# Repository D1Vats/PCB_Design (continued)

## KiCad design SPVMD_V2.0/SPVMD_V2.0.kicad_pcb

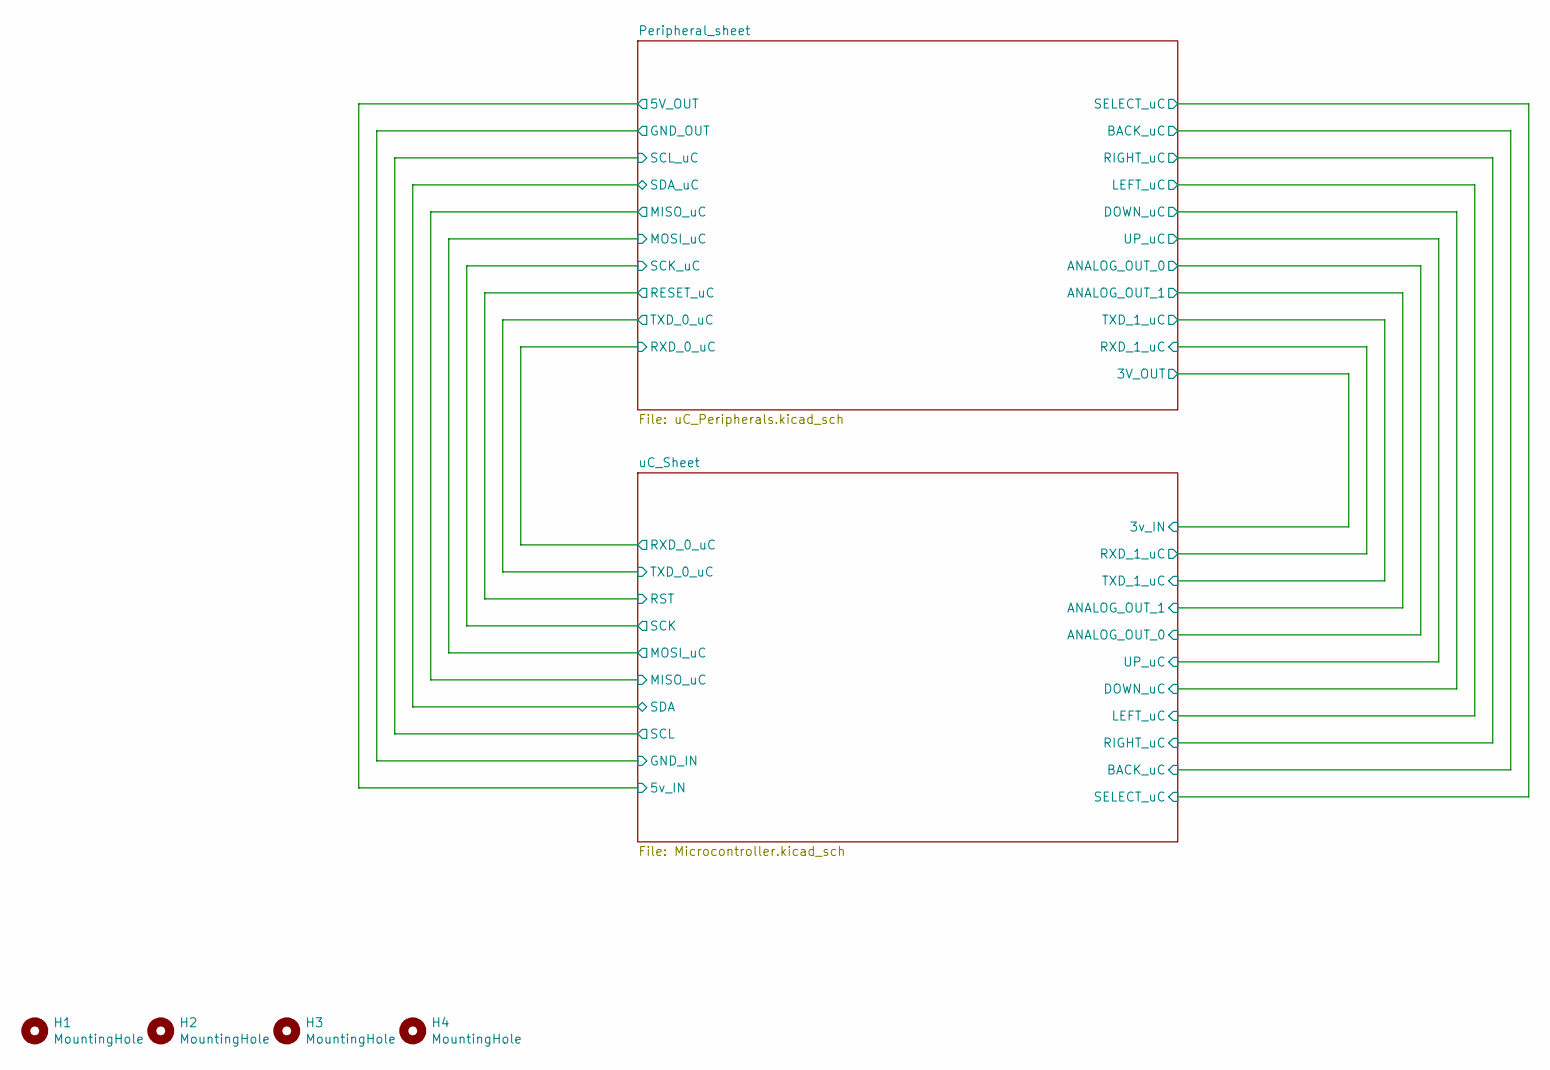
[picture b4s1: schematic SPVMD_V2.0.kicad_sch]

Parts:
H1, H2, H3, H4: MountingHole; MountingHole_3.2mm_M3

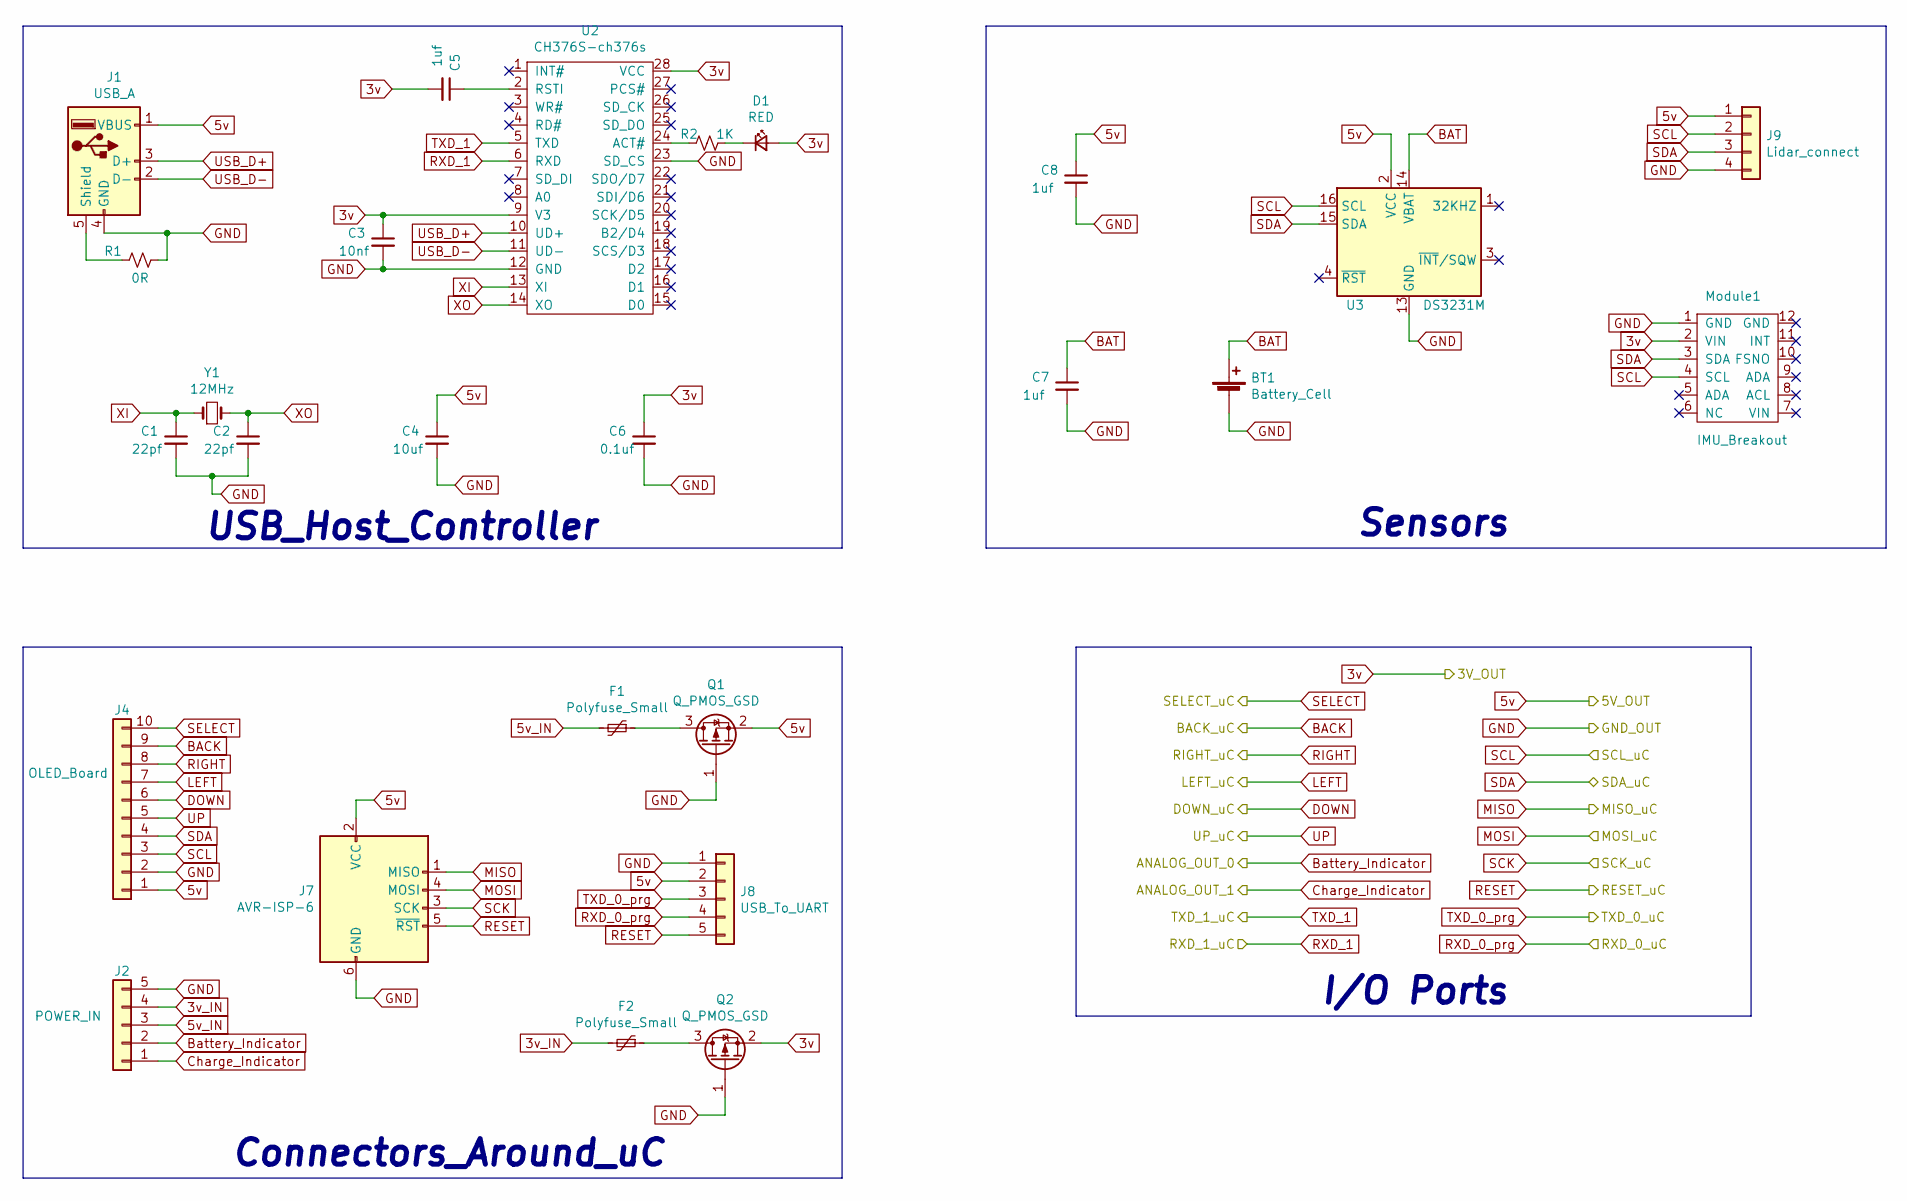
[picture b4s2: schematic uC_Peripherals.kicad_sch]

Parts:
BT1: Battery_Cell; BatteryHolder_Keystone_104_1x23mm
C1, C2: 22pf; C_0805_2012Metric
C3: 10nf; C_0805_2012Metric
C4: 10uf; C_0805_2012Metric
C5, C7, C8: 1uf; C_0805_2012Metric
C6: 0.1uf; C_0805_2012Metric
D1: RED; LED_0805_2012Metric
F1, F2: Polyfuse_Small; Fuse_0805_2012Metric_Pad1.15x1.40mm_HandSolder
J1: USB_A; USB_A_Molex_67643_Horizontal
J2: POWER_IN; SolderWire-0.1sqmm_1x05_P3.6mm_D0.4mm_OD1mm_Relief
J4: OLED_Board; Hirose_FH12-10S-0.5SH_1x10-1MP_P0.50mm_Horizontal
J7: AVR-ISP-6; PinHeader_2x03_P2.54mm_Vertical
J8: USB_To_UART; PinSocket_1x05_P2.54mm_Vertical
J9: Lidar_connect; SolderWire-0.1sqmm_1x04_P3.6mm_D0.4mm_OD1mm_Relief
Module1: IMU_Breakout; DIP-12_925_ELL
Q1, Q2: Q_PMOS_GSD; SOT-23W_Handsoldering
R1: 0R; R_0805_2012Metric
R2: 1K; R_0805_2012Metric
U2: CH376S-ch376s; SOIC-28W_7.5x17.9mm_P1.27mm
U3: DS3231M; SOIC-16W_7.5x10.3mm_P1.27mm
Y1: 12MHz; Crystal_HC49-4H_Vertical

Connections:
3V_IN: C3.1, C5.2, C6.1, D1.2 (A), Module1.2 (VIN), Q2.2 (S), U2.9 (V3), U2.28 (VCC); also elsewhere on the board
3v_IN: F2.2, J2.4
5v: C4.1, C8.1, J1.1 (VBUS), J4.1, J7.2 (VCC), J8.2, J9.1, Q1.2 (S), U3.2 (VCC); also elsewhere on the board
5v_IN: F1.2, J2.3
BACK: J4.9; also elsewhere on the board
BAT: BT1.1 (+), C7.1, U3.14 (VBAT)
Battery_Indicator: J2.2; also elsewhere on the board
Charge_Indicator: J2.1; also elsewhere on the board
DOWN: J4.6; also elsewhere on the board
GND: BT1.2 (-), C1.2, C2.2, C3.2, C4.2, C6.2, C7.2, C8.2, J1.4 (GND), J2.5, J4.2, J7.6 (GND), J8.1, J9.4, Module1.1 (GND), Q1.1 (G), Q2.1 (G), R1.1, U2.12 (GND), U2.23 (SD_CS), U3.5 (GND), U3.6 (GND), U3.7 (GND), U3.8 (GND), U3.9 (GND), U3.10 (GND), U3.11 (GND), U3.12 (GND), U3.13 (GND); also elsewhere on the board
LEFT: J4.7; also elsewhere on the board
LV_RXD_1: U2.5 (TXD); also elsewhere on the board
LV_TXD_1: U2.6 (RXD); also elsewhere on the board
MISO: J7.1 (MISO); also elsewhere on the board
MOSI: J7.4 (MOSI); also elsewhere on the board
unnamed: C5.1, U2.2 (RSTI)
unnamed: D1.1 (K), R2.1
unnamed: F1.1, Q1.3 (D)
unnamed: F2.1, Q2.3 (D)
unnamed: J1.5 (Shield), R1.2
unnamed: R2.2, U2.24 (ACT#)
RESET: J7.5 (~RST), J8.5; also elsewhere on the board
RIGHT: J4.8; also elsewhere on the board
RXD_0: J8.3; also elsewhere on the board
RXD_0_prg: J8.4; also elsewhere on the board
SCK: J7.3 (SCK); also elsewhere on the board
SCL: J4.3, J9.2, Module1.4 (SCL), U3.16 (SCL); also elsewhere on the board
SDA: J4.4, J9.3, Module1.3 (SDA), U3.15 (SDA); also elsewhere on the board
SELECT: J4.10; also elsewhere on the board
UP: J4.5; also elsewhere on the board
USB_D+: J1.3 (D+), U2.10 (UD+)
USB_D-: J1.2 (D-), U2.11 (UD-)
XI: C1.1, U2.13 (XI), Y1.1
XO: C2.1, U2.14 (XO), Y1.2

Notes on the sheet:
Connectors_Around_uC
USB_Host_Controller
I/O Ports
Sensors

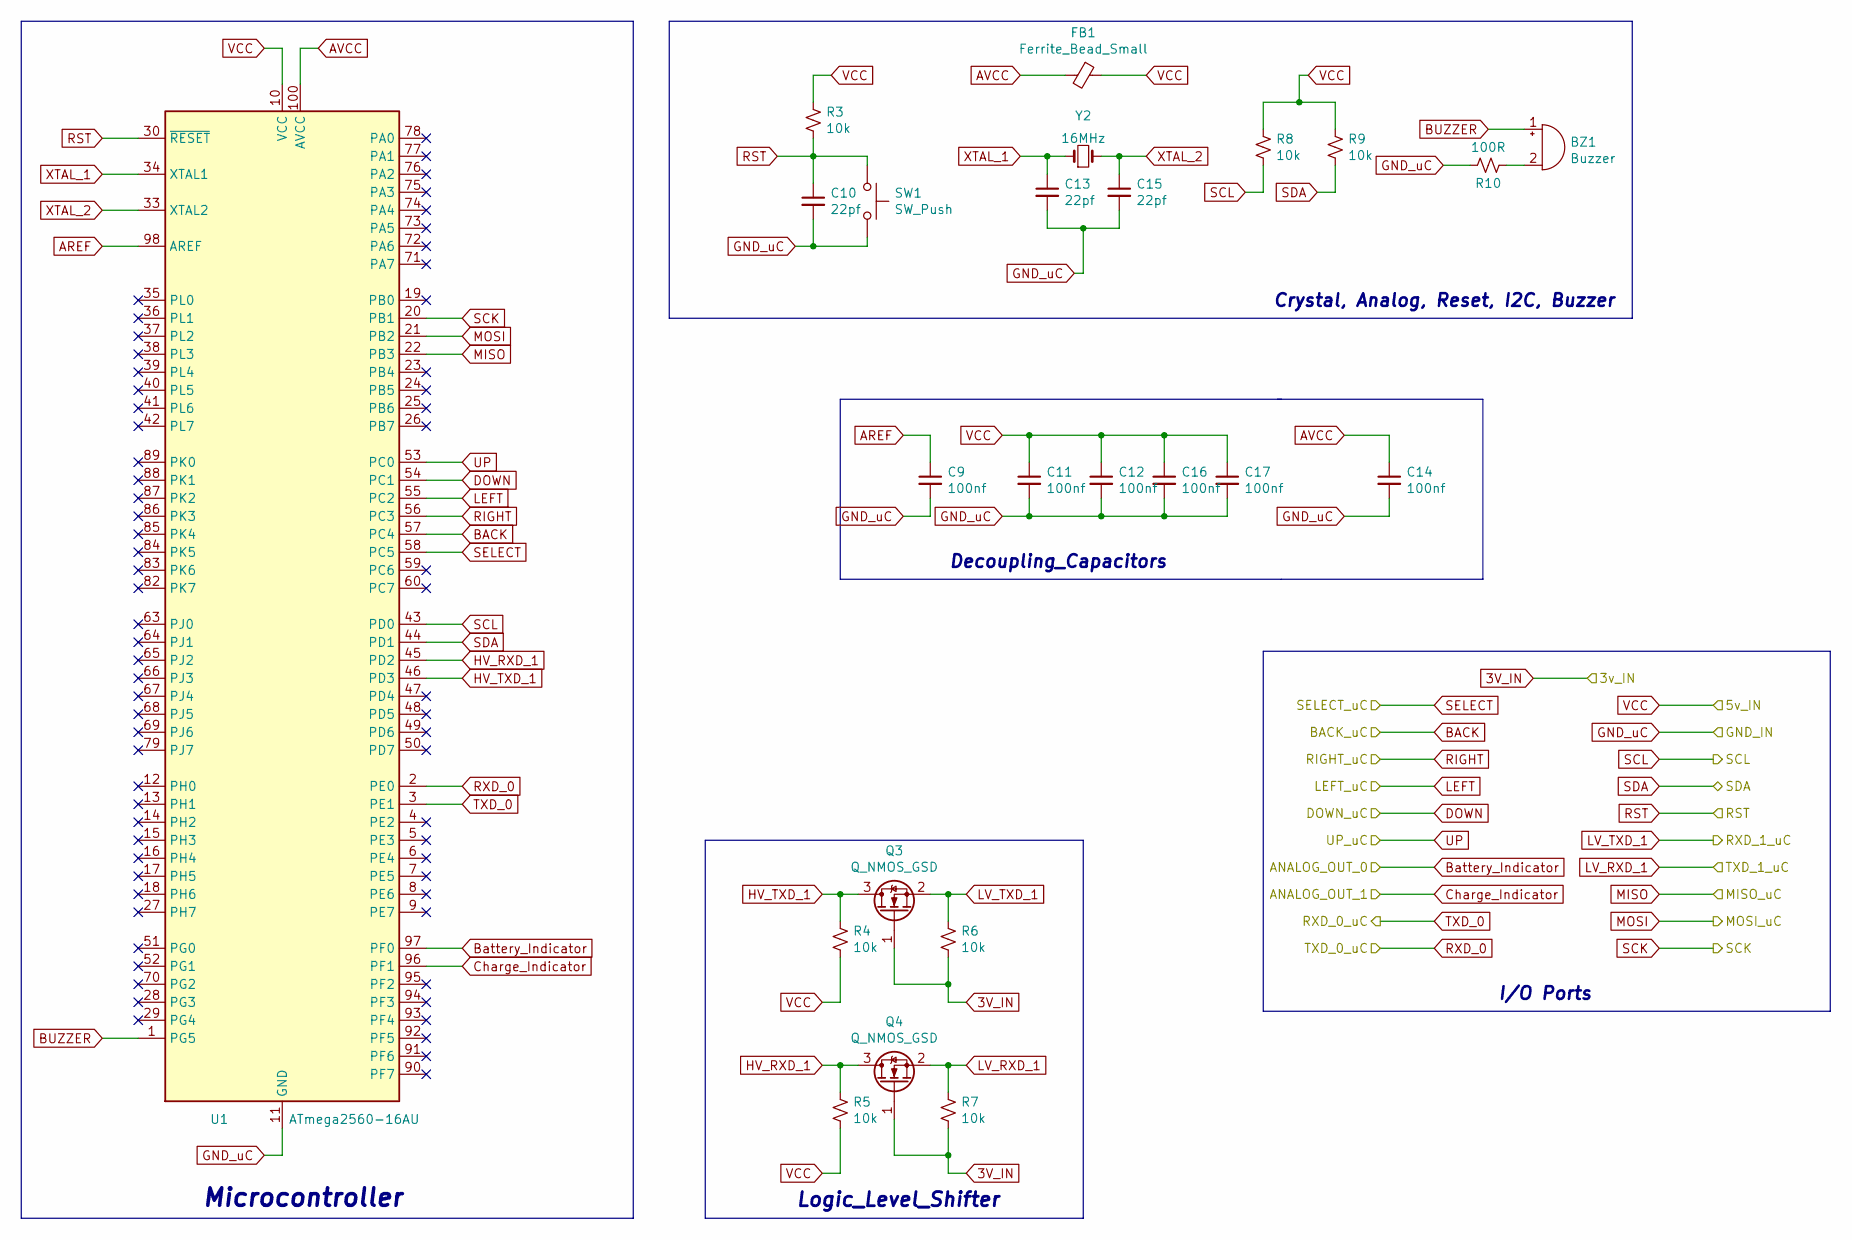
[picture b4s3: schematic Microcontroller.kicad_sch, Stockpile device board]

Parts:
BZ1: Buzzer; Buzzer_12x9.5RM7.6
C9, C11, C12, C14, C16, C17: 100nf; C_0805_2012Metric
C10, C13, C15: 22pf; C_0805_2012Metric
FB1: Ferrite_Bead_Small; R_0805_2012Metric
Q3, Q4: Q_NMOS_GSD; SOT-23W_Handsoldering
R3, R4, R5, R6, R7, R8, R9: 10k; R_0805_2012Metric
R10: 100R; R_0805_2012Metric
SW1: SW_Push; SW_PUSH_6mm
U1: ATmega2560-16AU; TQFP-100_14x14mm_P0.5mm
Y2: 16MHz; Crystal_HC49-4H_Vertical

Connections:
3V_IN: Q3.1 (G), Q4.1 (G), R6.2, R7.2; also elsewhere on the board
5v: C11.1, C12.1, C16.1, C17.1, FB1.1, R3.1, R4.2, R5.2, R8.1, R9.1, U1.10 (VCC), U1.31 (VCC), U1.61 (VCC), U1.80 (VCC); also elsewhere on the board
AREF: C9.1, U1.98 (AREF)
AVCC: C14.1, FB1.2, U1.100 (AVCC)
BACK: U1.57 (PC4); also elsewhere on the board
BUZZER: BZ1.1 (-), U1.1 (PG5)
Battery_Indicator: U1.97 (PF0); also elsewhere on the board
Charge_Indicator: U1.96 (PF1); also elsewhere on the board
DOWN: U1.54 (PC1); also elsewhere on the board
GND: C9.2, C10.2, C11.2, C12.2, C13.2, C14.2, C15.2, C16.2, C17.2, R10.2, SW1.2, U1.11 (GND), U1.32 (GND), U1.62 (GND), U1.81 (GND), U1.99 (GND); also elsewhere on the board
HV_RXD_1: Q4.3 (D), R5.1, U1.45 (PD2)
HV_TXD_1: Q3.3 (D), R4.1, U1.46 (PD3)
LEFT: U1.55 (PC2); also elsewhere on the board
LV_RXD_1: Q4.2 (S), R7.1; also elsewhere on the board
LV_TXD_1: Q3.2 (S), R6.1; also elsewhere on the board
MISO: U1.22 (PB3); also elsewhere on the board
MOSI: U1.21 (PB2); also elsewhere on the board
unnamed: BZ1.2 (+), R10.1
RESET: C10.1, R3.2, SW1.1, U1.30 (~RESET); also elsewhere on the board
RIGHT: U1.56 (PC3); also elsewhere on the board
RXD_0: U1.2 (PE0); also elsewhere on the board
RXD_0_prg: U1.3 (PE1); also elsewhere on the board
SCK: U1.20 (PB1); also elsewhere on the board
SCL: R8.2, U1.43 (PD0); also elsewhere on the board
SDA: R9.2, U1.44 (PD1); also elsewhere on the board
SELECT: U1.58 (PC5); also elsewhere on the board
UP: U1.53 (PC0); also elsewhere on the board
XTAL_1: C13.1, U1.34 (XTAL1), Y2.1
XTAL_2: C15.1, U1.33 (XTAL2), Y2.2

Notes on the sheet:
Decoupling_Capacitors
Microcontroller
Logic_Level_Shifter
I/O Ports
Crystal, Analog, Reset, I2C, Buzzer

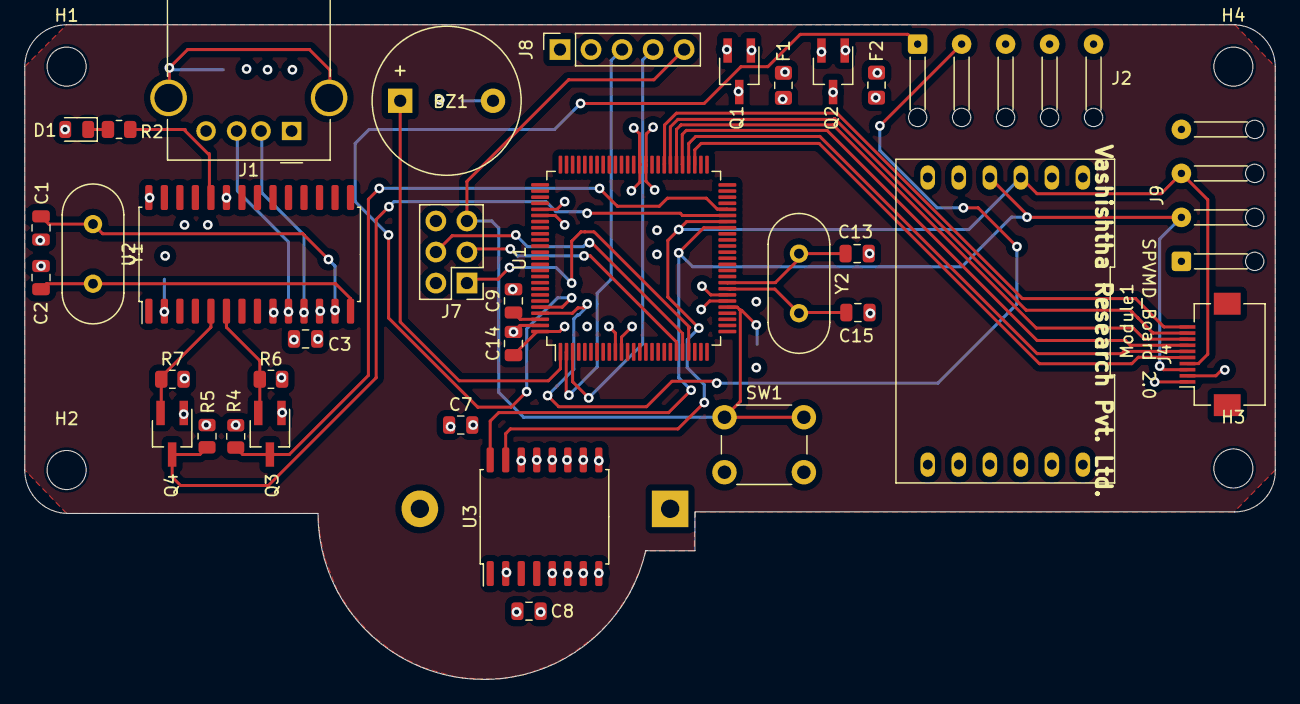
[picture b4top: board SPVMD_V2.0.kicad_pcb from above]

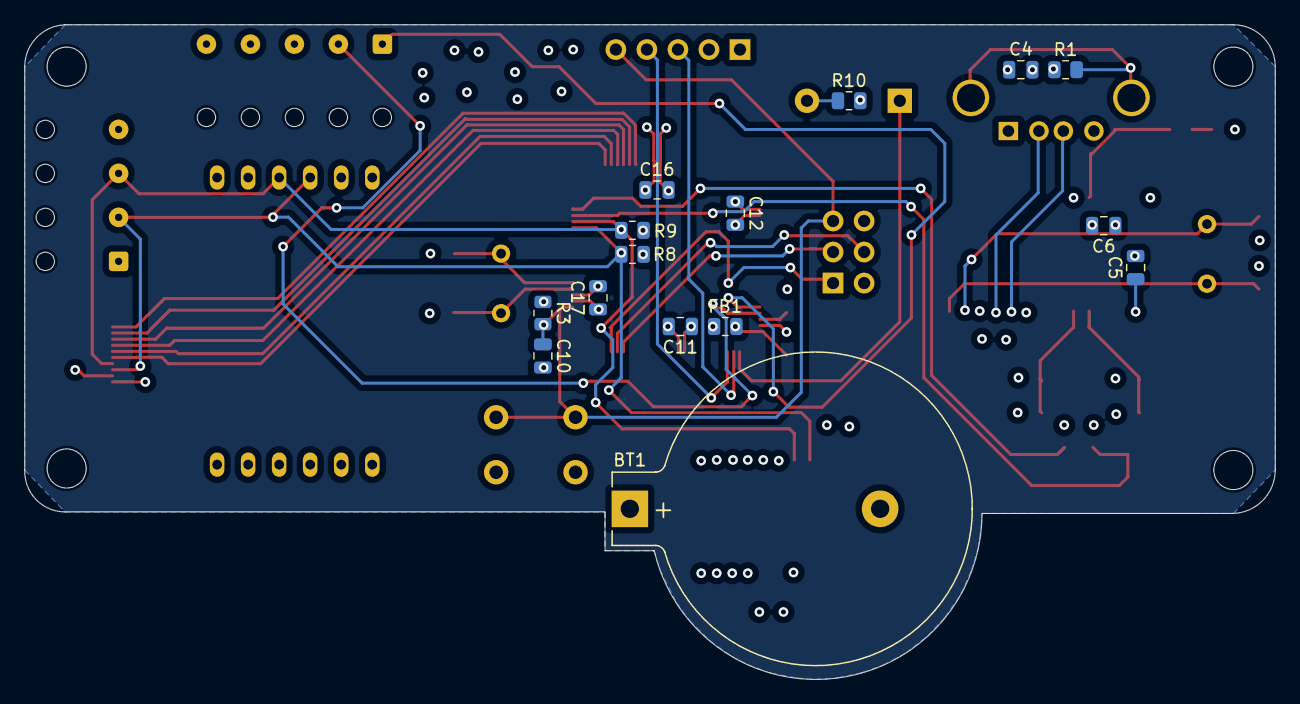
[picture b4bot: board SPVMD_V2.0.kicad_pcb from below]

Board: 4 copper layers, 102.4 x 53.6 mm, 54 parts (15 on the bottom side), 42 nets.

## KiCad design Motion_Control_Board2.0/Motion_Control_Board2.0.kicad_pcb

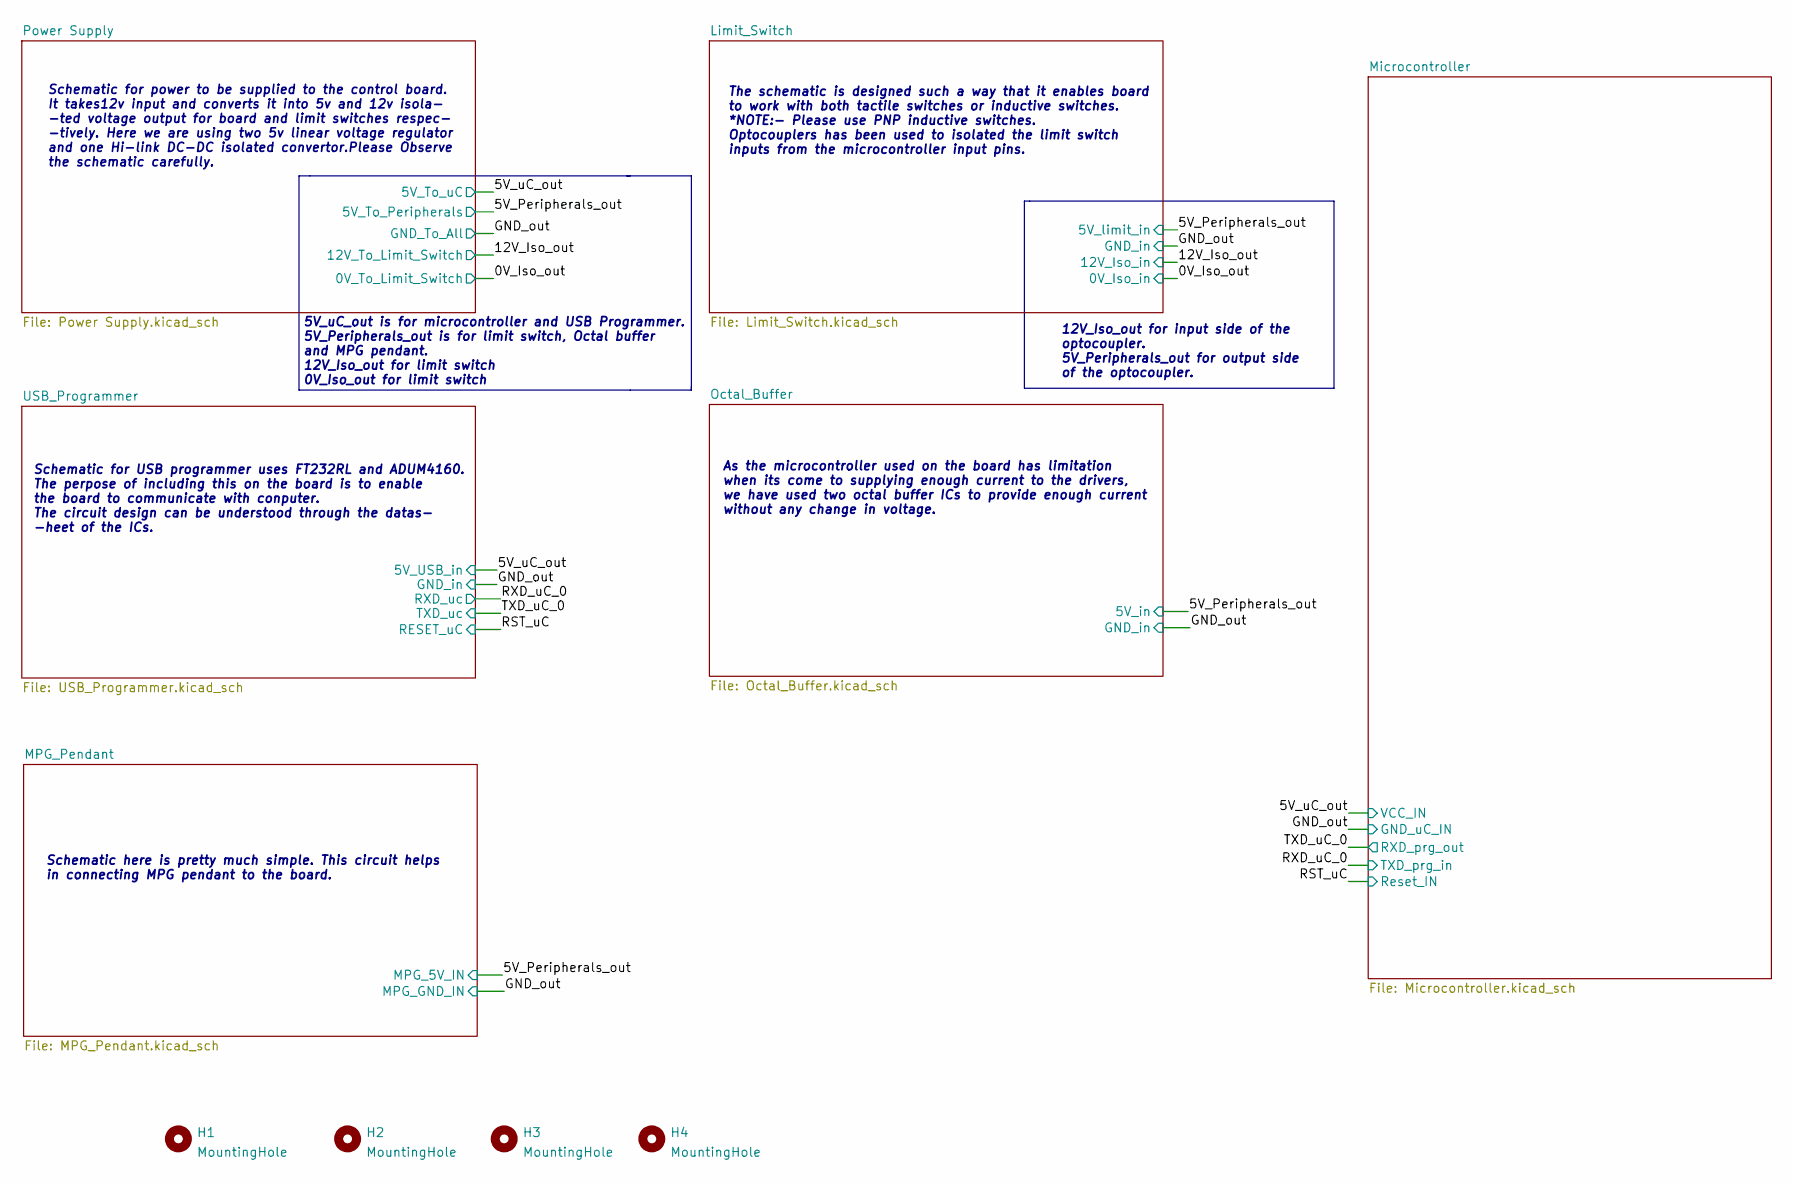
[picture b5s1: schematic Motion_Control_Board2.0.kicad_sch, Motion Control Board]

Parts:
H1, H2, H3, H4: MountingHole; MountingHole_3.2mm_M3

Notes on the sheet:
Schematic here is pretty much simple. This circuit helps in connecting MPG pendant to the board.
Schematic for USB programmer uses FT232RL and ADUM4160. The perpose of including this on the board is to enable the board to communicate with conputer. The circuit design can be understood through the datas- -heet of the ICs.
12V_Iso_out for input side of the optocoupler. 5V_Peripherals_out for output side of the optocoupler.
As the microcontroller used on the board has limitation when its come to supplying enough current to the drivers, we have used two octal buffer ICs to provide enough current without any change in voltage.
Schematic for power to be supplied to the control board. It takes12v input and converts it into 5v and 12v isola- -ted voltage output for board and limit switches respec- -tively. Here we are using two 5v linear voltage regulator and one Hi-link DC-DC isolated convertor.Please Observe the schematic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
The schematic is designed such a way that it enables board to work with both tactile switches or inductive switches. *NOTE:- Please use PNP inductive switches. Optocouplers has been used to isolated the limit switch inputs from the microcontroller input pins.
5V_uC_out is for microcontroller and USB Programmer. 5V_Peripherals_out is for limit switch, Octal buffer and MPG pendant. 12V_Iso_out for limit switch 0V_Iso_out for limit switch

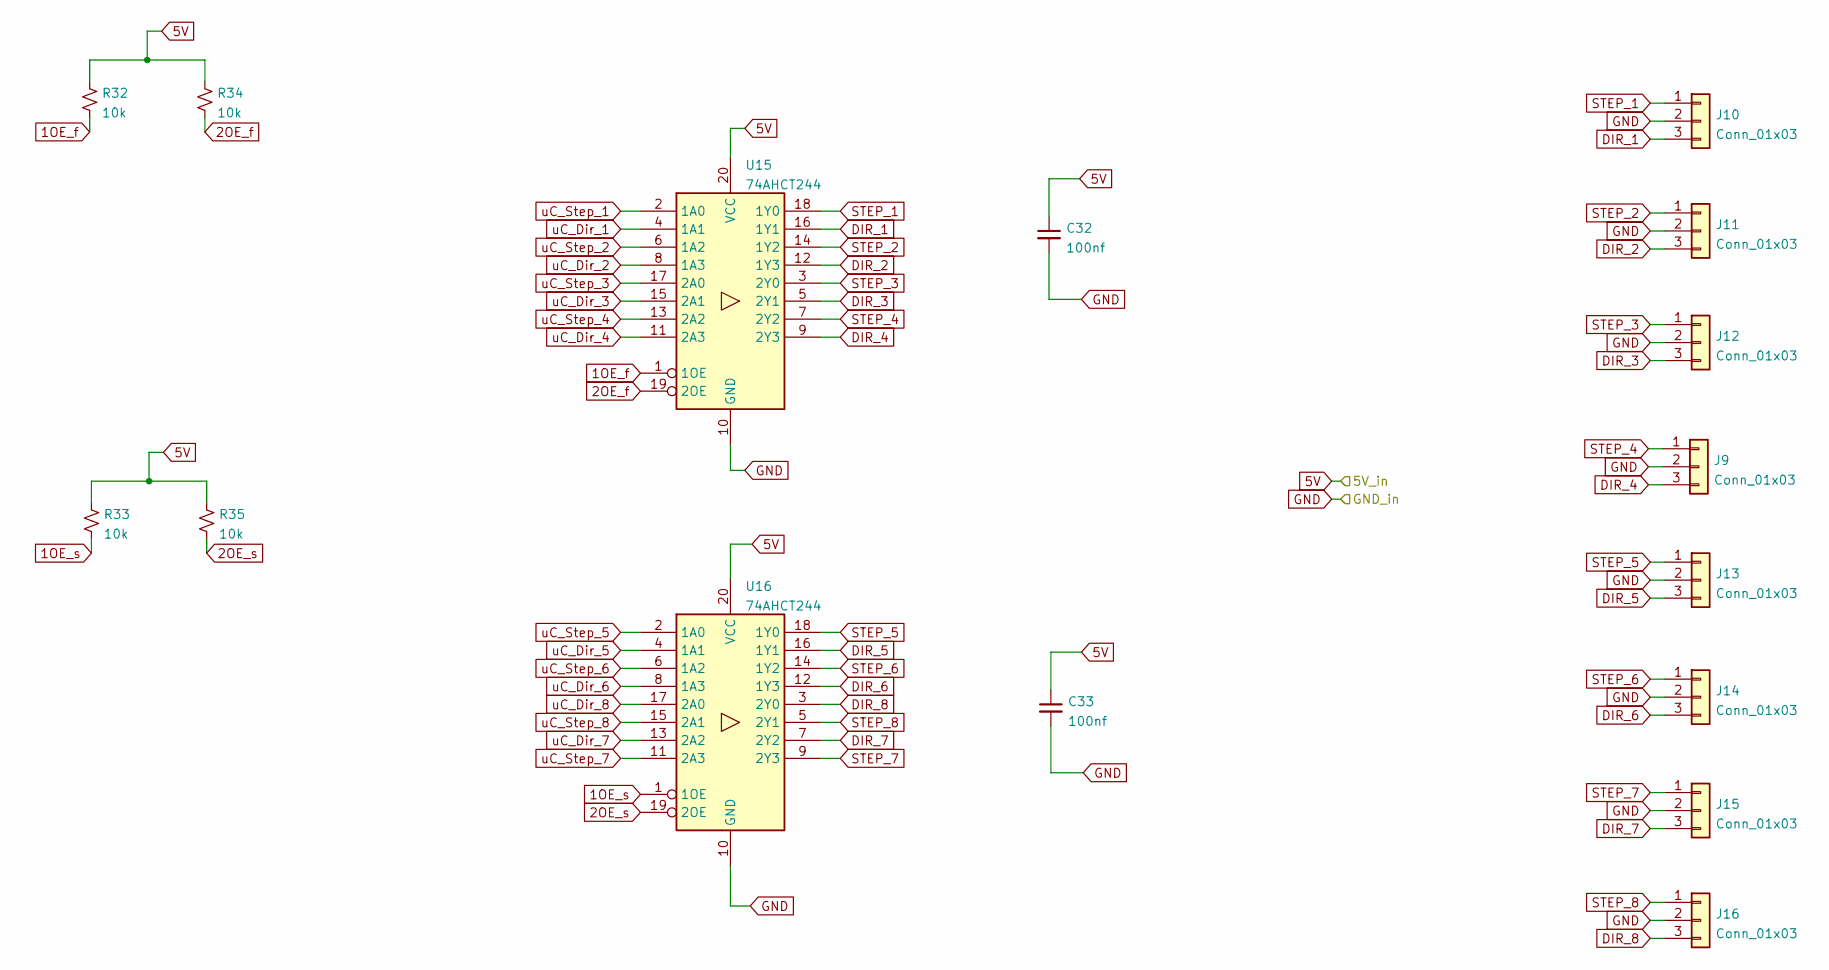
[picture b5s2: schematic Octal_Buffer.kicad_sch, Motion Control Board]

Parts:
C32, C33: 100nf; C_0805_2012Metric
J9, J10, J11, J12, J13, J14, J15, J16: Conn_01x03; TerminalBlock_4Ucon_1x03_P3.50mm_Vertical
R32, R33, R34, R35: 10k; R_0805_2012Metric
U15, U16: 74AHCT244; SOIC-20W_7.5x12.8mm_P1.27mm

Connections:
1OE_f: R32.2, U15.1 (1OE); also elsewhere on the board
1OE_s: R33.2, U16.1 (1OE); also elsewhere on the board
2OE_f: R34.2, U15.19 (2OE); also elsewhere on the board
2OE_s: R35.2, U16.19 (2OE); also elsewhere on the board
5V_OUT_2: C32.1, C33.1, R32.1, R33.1, R34.1, R35.1, U15.20 (VCC), U16.20 (VCC); also elsewhere on the board
DIR_1: J10.3, U15.16 (1Y1)
DIR_2: J11.3, U15.12 (1Y3)
DIR_3: J12.3, U15.5 (2Y1)
DIR_4: J9.3, U15.9 (2Y3)
DIR_5: J13.3, U16.16 (1Y1)
DIR_6: J14.3, U16.12 (1Y3)
DIR_7: J15.3, U16.7 (2Y2)
DIR_8: J16.3, U16.3 (2Y0)
MPG_GND: C32.2, C33.2, J9.2, J10.2, J11.2, J12.2, J13.2, J14.2, J15.2, J16.2, U15.10 (GND), U16.10 (GND); also elsewhere on the board
STEP_1: J10.1, U15.18 (1Y0)
STEP_2: J11.1, U15.14 (1Y2)
STEP_3: J12.1, U15.3 (2Y0)
STEP_4: J9.1, U15.7 (2Y2)
STEP_5: J13.1, U16.18 (1Y0)
STEP_6: J14.1, U16.14 (1Y2)
STEP_7: J15.1, U16.9 (2Y3)
STEP_8: J16.1, U16.5 (2Y1)
uC_Dir_1: U15.4 (1A1); also elsewhere on the board
uC_Dir_2: U15.8 (1A3); also elsewhere on the board
uC_Dir_3: U15.15 (2A1); also elsewhere on the board
uC_Dir_4: U15.11 (2A3); also elsewhere on the board
uC_Dir_5: U16.4 (1A1); also elsewhere on the board
uC_Dir_6: U16.8 (1A3); also elsewhere on the board
uC_Dir_7: U16.13 (2A2); also elsewhere on the board
uC_Dir_8: U16.17 (2A0); also elsewhere on the board
uC_Step_1: U15.2 (1A0); also elsewhere on the board
uC_Step_2: U15.6 (1A2); also elsewhere on the board
uC_Step_3: U15.17 (2A0); also elsewhere on the board
uC_Step_4: U15.13 (2A2); also elsewhere on the board
uC_Step_5: U16.2 (1A0); also elsewhere on the board
uC_Step_6: U16.6 (1A2); also elsewhere on the board
uC_Step_7: U16.11 (2A3); also elsewhere on the board
uC_Step_8: U16.15 (2A1); also elsewhere on the board

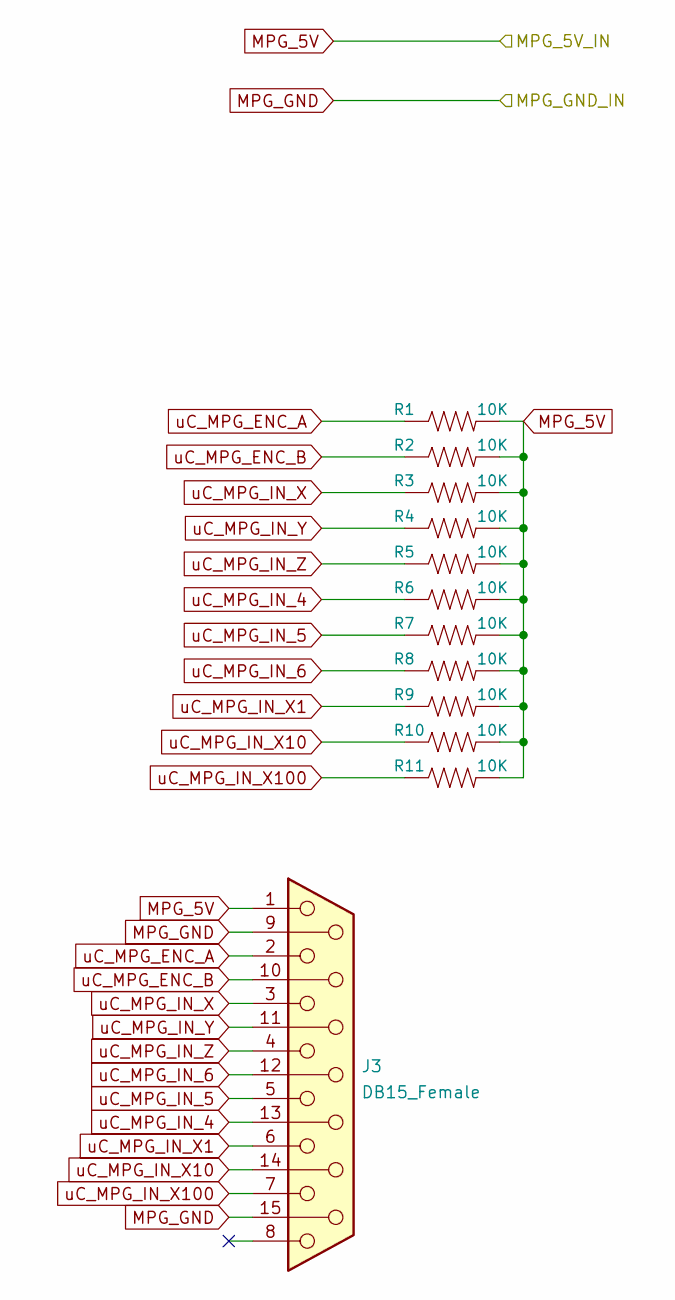
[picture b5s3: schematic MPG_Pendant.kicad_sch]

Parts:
J3: DB15_Female; DSUB-15_Female_Horizontal_P2.77x2.84mm_EdgePinOffset7.70mm_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
R1, R2, R3, R4, R5, R6, R7, R8, R9, R10, R11: 10K; R_0805_2012Metric

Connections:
5V_OUT_2: J3.1, R1.2, R2.2, R3.2, R4.2, R5.2, R6.2, R7.2, R8.2, R9.2, R10.2, R11.2; also elsewhere on the board
MPG_GND: J3.9, J3.15; also elsewhere on the board
uC_MPG_ENC_A: J3.2, R1.1; also elsewhere on the board
uC_MPG_ENC_B: J3.10, R2.1; also elsewhere on the board
uC_MPG_IN_4: J3.13, R6.1; also elsewhere on the board
uC_MPG_IN_5: J3.5, R7.1; also elsewhere on the board
uC_MPG_IN_6: J3.12, R8.1; also elsewhere on the board
uC_MPG_IN_X: J3.3, R3.1; also elsewhere on the board
uC_MPG_IN_X1: J3.6, R9.1; also elsewhere on the board
uC_MPG_IN_X10: J3.14, R10.1; also elsewhere on the board
uC_MPG_IN_X100: J3.7, R11.1; also elsewhere on the board
uC_MPG_IN_Y: J3.11 (P111), R4.1; also elsewhere on the board
uC_MPG_IN_Z: J3.4, R5.1; also elsewhere on the board

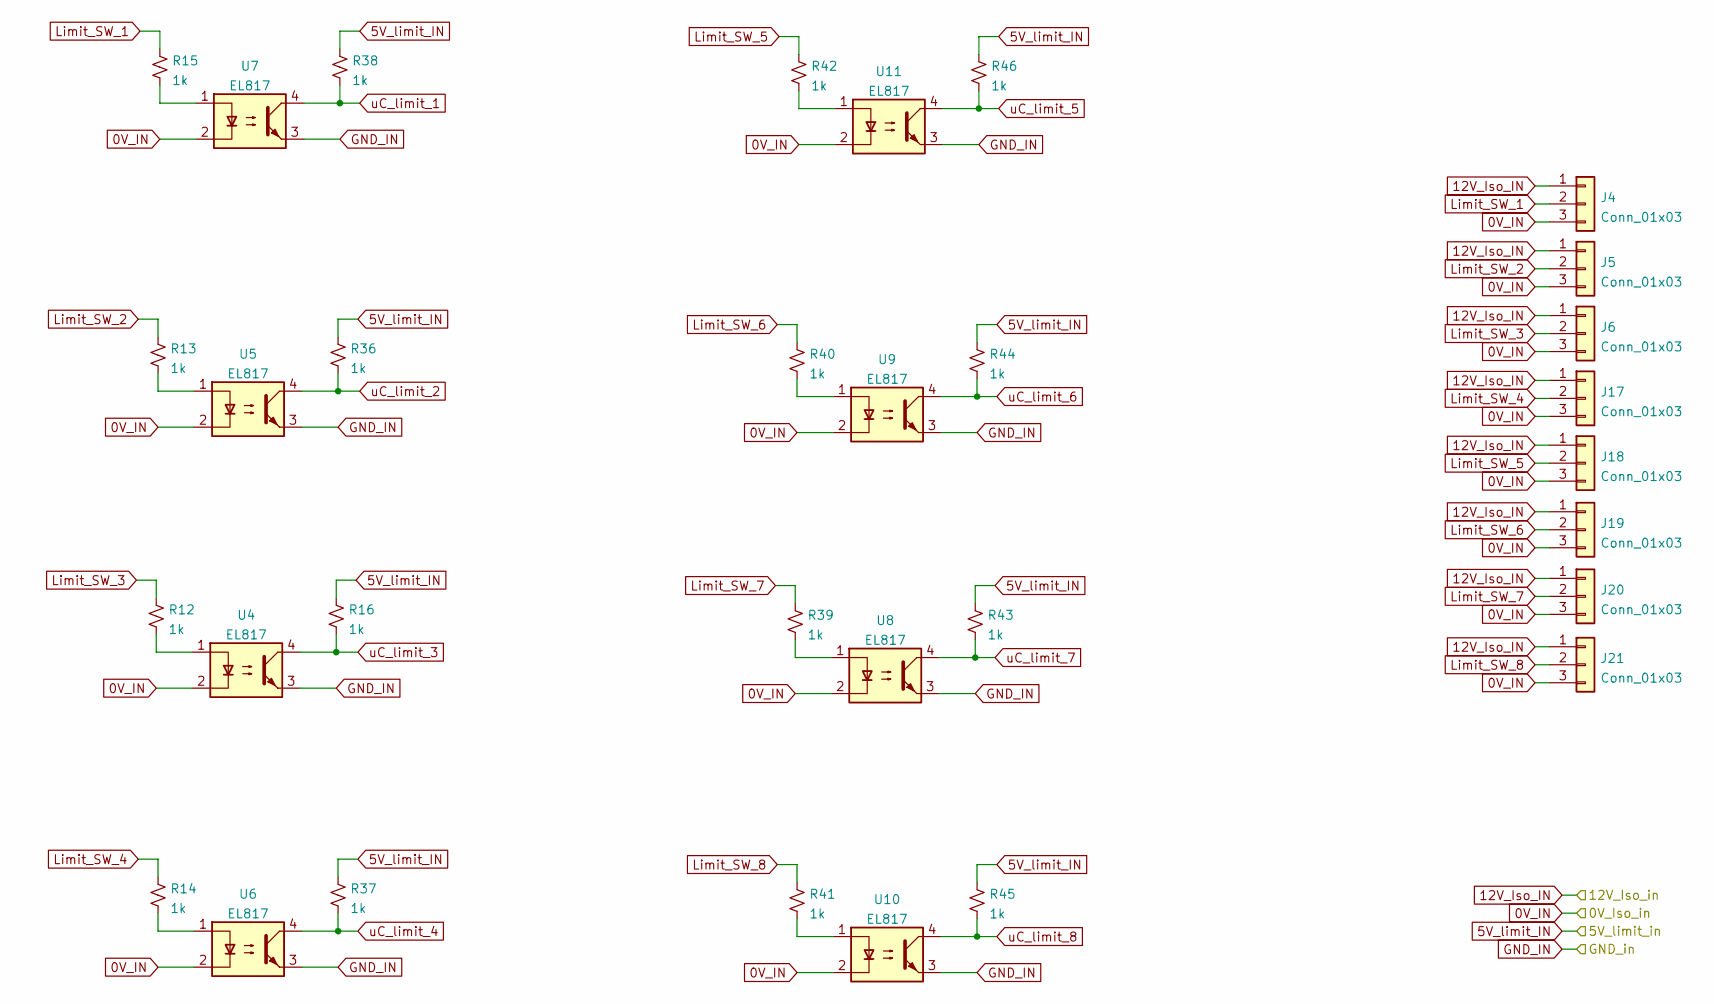
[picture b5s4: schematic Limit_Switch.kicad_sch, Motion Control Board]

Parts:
J4, J5, J6, J17, J18, J19, J20, J21: Conn_01x03; TerminalBlock_4Ucon_1x03_P3.50mm_Vertical
R12, R13, R14, R15, R16, R36, R37, R38, R39, R40, R41, R42, R43, R44, R45, R46: 1k; R_0805_2012Metric
U4, U5, U6, U7, U8, U9, U10, U11: EL817; SO-4_4.4x3.6mm_P2.54mm

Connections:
0V_OUT: J4.3, J5.3, J6.3, J17.3, J18.3, J19.3, J20.3, J21.3, U4.2, U5.2, U6.2, U7.2, U8.2, U9.2, U10.2, U11.2; also elsewhere on the board
5V_OUT_2: R16.1, R36.1, R37.1, R38.1, R43.1, R44.1, R45.1, R46.1; also elsewhere on the board
12V_OUT: J4.1, J5.1, J6.1, J17.1, J18.1, J19.1, J20.1, J21.1; also elsewhere on the board
Limit_SW_1: J4.2, R15.1
Limit_SW_2: J5.2, R13.1
Limit_SW_3: J6.2, R12.1
Limit_SW_4: J17.2, R14.1
Limit_SW_5: J18.2, R42.1
Limit_SW_6: J19.2, R40.1
Limit_SW_7: J20.2, R39.1
Limit_SW_8: J21.2, R41.1
MPG_GND: U4.3, U5.3, U6.3, U7.3, U8.3, U9.3, U10.3, U11.3; also elsewhere on the board
unnamed: R12.2, U4.1
unnamed: R13.2, U5.1
unnamed: R14.2, U6.1
unnamed: R15.2, U7.1
unnamed: R39.2, U8.1
unnamed: R40.2, U9.1
unnamed: R41.2, U10.1
unnamed: R42.2, U11.1
uC_limit_1: R38.2, U7.4; also elsewhere on the board
uC_limit_2: R36.2, U5.4; also elsewhere on the board
uC_limit_3: R16.2, U4.4; also elsewhere on the board
uC_limit_4: R37.2, U6.4; also elsewhere on the board
uC_limit_5: R46.2, U11.4; also elsewhere on the board
uC_limit_6: R44.2, U9.4; also elsewhere on the board
uC_limit_7: R43.2, U8.4; also elsewhere on the board
uC_limit_8: R45.2, U10.4; also elsewhere on the board
